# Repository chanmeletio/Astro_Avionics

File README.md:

# Astro at Baylor — Avionics Subsystem

Flight computer, sensor acquisition, dual-deployment recovery actuation, and telemetry subsystem developed by **Astro at Baylor** for the **2027 Intercollegiate Rocket Engineering Competition (IREC)** at Spaceport America.

---

## Subsystem Architecture

```
Astro_Avionics/
├── .github/
│   ├── workflows/          # Automated CI/CD (KiCad v10 DRC/ERC, ARM GCC cross-compilation)
│   ├── ISSUE_TEMPLATE/     # Hardware ECO, firmware bug, and flight anomaly reports
│   └── PULL_REQUEST_TEMPLATE.md
├── docs/                   # Flight documentation, state machines, pinouts, and link budgets
├── firmware/
│   ├── app/                # Flight state machine, telemetry dispatcher, and mission logic
│   ├── bsp/                # Board Support Package for Astro Flight Computer
│   ├── cube/               # STM32CubeMX HAL initialization and CMSIS DSP libraries
│   ├── drivers/            # Sensor drivers (Baro, High-G & Low-G IMUs, GPS, Radio, MicroSD)
│   ├── mid/                # Middleware (ring buffers, comms framing, RTOS abstractions)
│   └── tests/              # Native host unit tests and simulation mocks
├── ground-station/         # Real-time telemetry receiver, packet decoder, and mission UI
├── hardware/
│   ├── drc/                # KiCad Design Rule constraints and automated DRC check scripts
│   ├── libraries/          # Custom team footprint, symbol, and 3D model libraries
│   └── rev_a/              # KiCad v10 Flight Controller schematics, layouts, and manufacturing outputs
└── sim/                    # Software-in-the-Loop (SITL) and Hardware-in-the-Loop (HIL) simulators
```

---

## Hardware Overview (Rev A)

The Astro Avionics Flight Controller is designed in **KiCad v10** to withstand high acceleration, vibration, and thermal environments typical of supersonic high-power rocket flights.

* **Primary Processing Unit**: STM32F405RGT6 (Arm Cortex-M4 with FPU @ 168 MHz)
* **Inertial Sensing**:
  * High-G Triaxial Accelerometer (high-velocity boost phase acquisition)
  * Low-G 6-DOF IMU (apogee detection, attitude estimation, and descent tracking)
* **Barometric Altimetry**: High-precision barometric pressure sensor for altitude & apogee determination
* **Recovery & Pyrotechnics**: Dual-deployment pyro firing channels (Drogue @ Apogee, Main @ configured AGL altitude) with hardware interlocks and live continuity sensing
* **Telemetry & RF**: Long-range transceiver for live flight telemetry packet transmission to the ground station
* **Non-Volatile Logging**: MicroSD card interface logging sensor telemetry at high rates

For complete design files, see [`hardware/rev_a/`](hardware/rev_a/).

---

## Toolchain & Developer Prerequisites

### 1. Hardware Engineering (KiCad EDA)
* **KiCad v10** (or compatible KiCad 10 nightly build)
* KiCad CLI (`kicad-cli`) installed on system PATH for running local DRC/ERC exports

### 2. Embedded Firmware
* **ARM Embedded Toolchain**: `arm-none-eabi-gcc` (v10+ recommended)
* **Build Systems**: `cmake` (v3.22+) and `ninja-build` or GNU `make`
* **Static Analysis**: `clang-format` and `cppcheck`
* **Flashing & Debugging**: ST-LINK / J-Link with `openocd` or STM32CubeProgrammer

### 3. Simulation & Ground Station
* **Python**: Python 3.10+ with `pip` and virtual environment support

---

## Quickstart Guide

### Building Firmware Locally
```bash
# Clone the repository
git clone https://github.com/chanmeletio/Astro_Avionics.git
cd Astro_Avionics

# Configure and build firmware
cmake -B firmware/build -S firmware -DCMAKE_TOOLCHAIN_FILE=cmake/arm-none-eabi.cmake -GNinja
cmake --build firmware/build
```

### Running Hardware DRC & ERC Headless
```bash
# Run KiCad Electrical Rules Check
kicad-cli sch erc --output hardware/rev_a/output/erc_report.json hardware/rev_a/New_Flight_Controller.kicad_sch

# Run KiCad Design Rules Check
kicad-cli pcb drc --output hardware/rev_a/output/drc_report.json hardware/rev_a/New_Flight_Controller.kicad_pcb

# Parse violations with gatekeeper script
python hardware/drc/drc-ci-check.py --drc hardware/rev_a/output/drc_report.json --erc hardware/rev_a/output/erc_report.json
```

---

## Safety Protocol & Mission Rules

> [!CAUTION]
> **Pyrotechnic Safety Interlock Rule**: No live e-matches or pyrotechnic charges may be connected to the flight computer in the laboratory without the physical arming key / safety shunt removed and verified with a multimeter. Live fire testing must strictly adhere to [`docs/safety_procedures.md`](docs/safety_procedures.md).

---

## Contributing & Development Workflow

1. Create a feature branch from `develop` (`feat/driver-bmi088`, `hw/rev-a-power-trace-update`).
2. Ensure DRC/ERC passes with zero errors before opening a pull request.
3. Submit a Pull Request targeting `develop` using the provided [Pull Request Template](.github/PULL_REQUEST_TEMPLATE.md).

## License

This project is licensed under the [MIT License](LICENSE).

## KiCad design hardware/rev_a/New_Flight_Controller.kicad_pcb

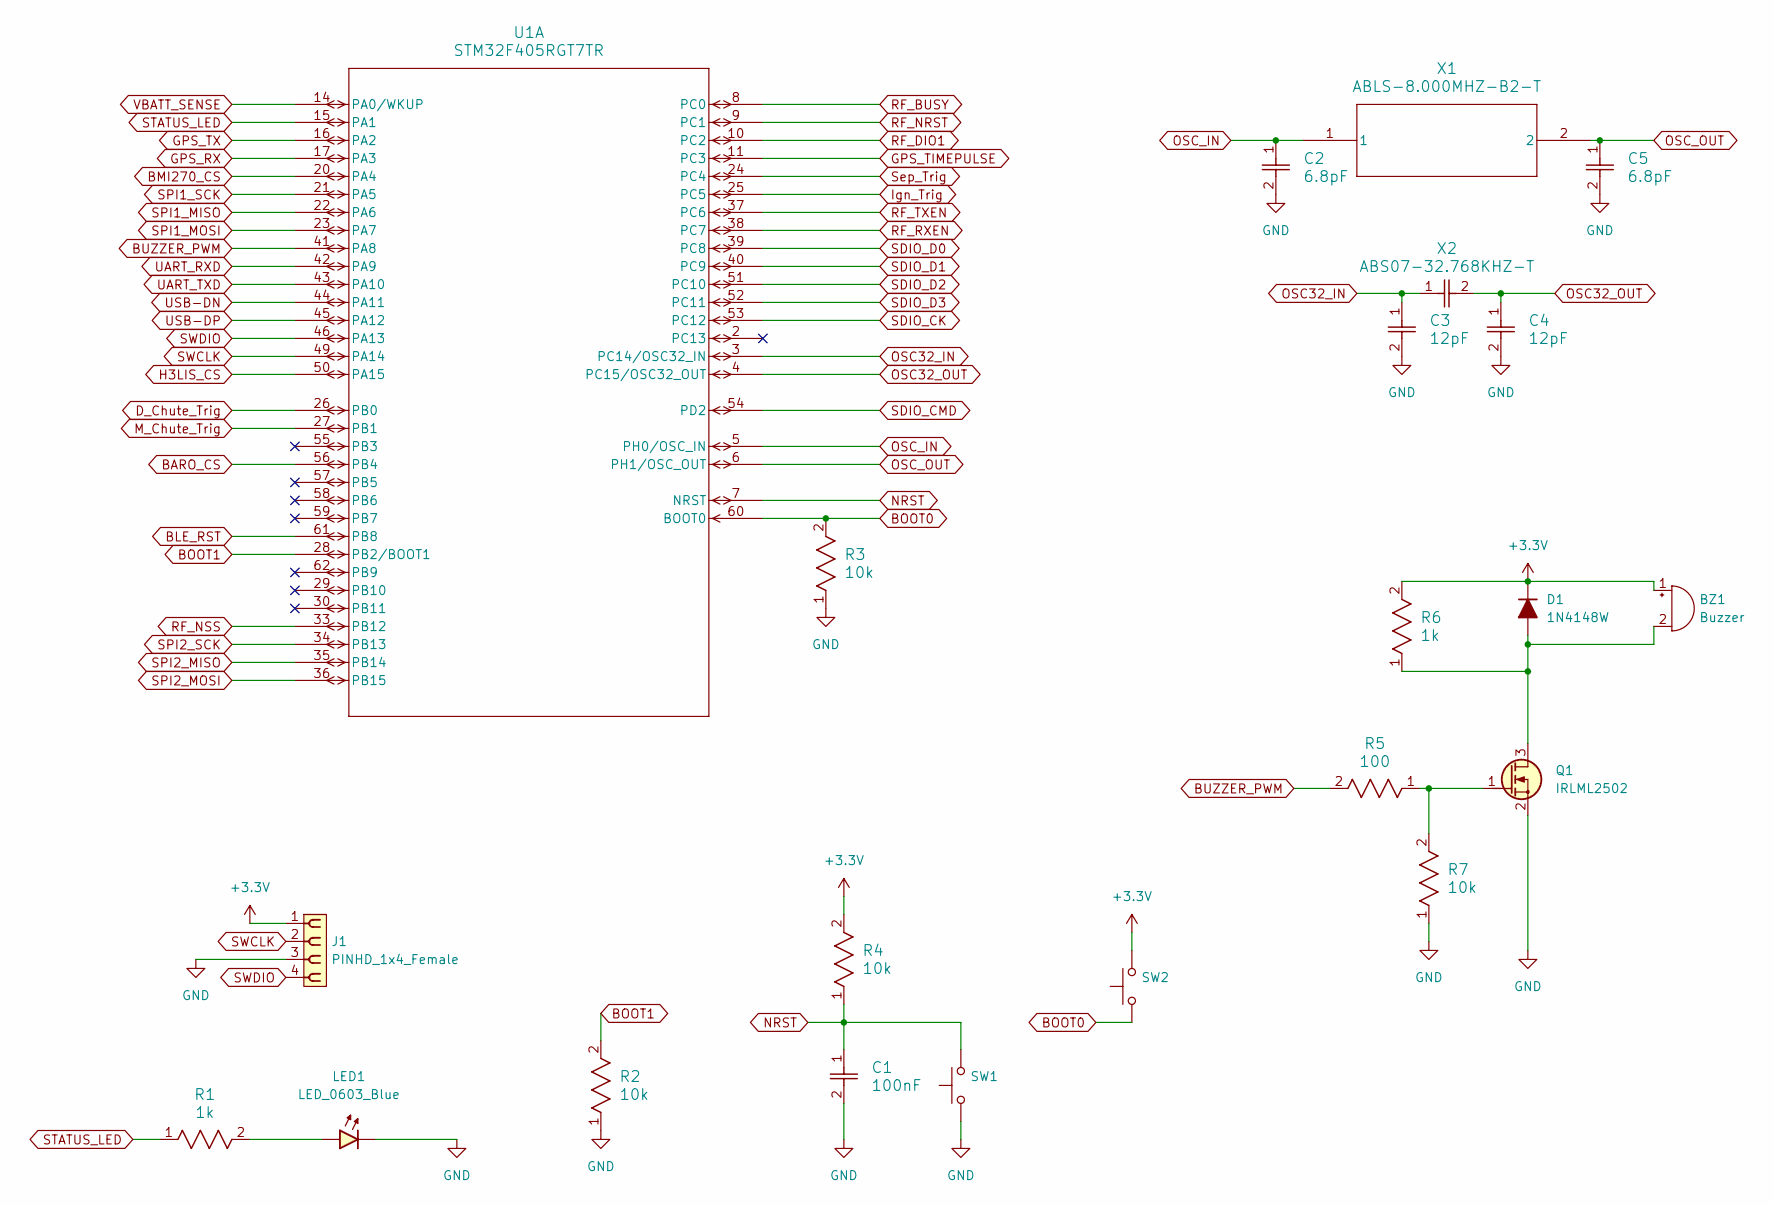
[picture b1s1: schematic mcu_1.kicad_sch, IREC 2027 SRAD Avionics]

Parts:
BZ1: Buzzer; Buzzer_Murata_PKMCS0909E; Mfg Part# PKMCS0909E4000-R1; JLCPCB Part # C910763
C1: 100nF; C_0603_1608Metric; Mfg Part# CL10B104KB8NNNC; JLCPCB Part # C1591
C2, C5: 6.8pF; C_0603_1608Metric; Mfg Part# CL10C6R8CB8NNNC; JLCPCB Part # C318672
C3, C4: 12pF; C_0603_1608Metric; Mfg Part# CL10C120JB8NNNC; JLCPCB Part # C38523
D1: 1N4148W; D_SOD-123; Mfg Part# 1N4148W; JLCPCB Part # C81598
J1: PINHD_1x4_Female; PinSocket_1x04_P2.54mm_Vertical; Mfg Part# 22850104ANG1SYA01; JLCPCB Part # C41431927
LED1: LED_0603_Blue; LED_0603_1608Metric; Mfg Part# KT-0603B; JLCPCB Part # C2288
Q1: IRLML2502; SOT-23; Mfg Part# IRLML2502TRPBF-ES; JLCPCB Part # C21713837
R1, R6: 1k; R_0603_1608Metric; Mfg Part# RC0603JR-071KL; JLCPCB Part # C14676
R2, R3, R4, R7: 10k; R_0603_1608Metric; Mfg Part# RC0603JR-0710KL; JLCPCB Part # C99198
R5: 100; R_0603_1608Metric; Mfg Part# RC0603FR-07100RL; JLCPCB Part # C105588
SW1, SW2: SW_Push_1P1T_NO_E-Switch_TL3301NxxxxxG; Mfg Part# 4-1437565-1; JLCPCB Part # C592734
U1: STM32F405RGT7TR; LQFP64-10x10mm; Mfg Part# STM32F405RGT7TR; JLCPCB Part # C2054405
X1: ABLS-8.000MHZ-B2-T; ABLS-8.000MHZ-B2-T_ABR; Mfg Part# ABLS-8.000MHZ-B2-T; JLCPCB Part # C596837
X2: ABS07-32.768KHZ-T; CAP_ABS07-32.768KHZ-T_ABR; Mfg Part# ABS07-32.768KHZ-T; JLCPCB Part # C130253

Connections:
+3.3V: BZ1.1 (+), D1.1 (K), J1.1, R4.2, R6.2, SW2.2; also elsewhere on the board
BARO_CS: U1.56 (PB4); also elsewhere on the board
BLE_RST: U1.61 (PB8); also elsewhere on the board
BMI270_CS: U1.20 (PA4); also elsewhere on the board
BOOT0: R3.2, SW2.1, U1.60 (BOOT0)
BOOT1: R2.2, U1.28 (PB2/BOOT1)
BUZZER_PWM: R5.2, U1.41 (PA8)
D_Chute_Trig: U1.26 (PB0); also elsewhere on the board
GND: C1.2, C2.2, C3.2, C4.2, C5.2, J1.3, LED1.1 (K), Q1.2 (S), R2.1, R3.1, R7.1, SW1.1; also elsewhere on the board
GPS_RX: U1.17 (PA3); also elsewhere on the board
GPS_TIMEPULSE: U1.11 (PC3); also elsewhere on the board
GPS_TX: U1.16 (PA2); also elsewhere on the board
H3LIS_CS: U1.50 (PA15); also elsewhere on the board
Ign_Trig: U1.25 (PC5); also elsewhere on the board
M_Chute_Trig: U1.27 (PB1); also elsewhere on the board
NRST: C1.1, R4.1, SW1.2, U1.7 (NRST)
unnamed: BZ1.2 (-), D1.2 (A), Q1.3 (D), R6.1
unnamed: LED1.2 (A), R1.2
unnamed: Q1.1 (G), R5.1, R7.2
OSC32_IN: C3.1, U1.3 (PC14/OSC32_IN), X2.1
OSC32_OUT: C4.1, U1.4 (PC15/OSC32_OUT), X2.2
OSC_IN: C2.1, U1.5 (PH0/OSC_IN), X1.1
OSC_OUT: C5.1, U1.6 (PH1/OSC_OUT), X1.2
RF_BUSY: U1.8 (PC0); also elsewhere on the board
RF_DIO1: U1.10 (PC2); also elsewhere on the board
RF_NRST: U1.9 (PC1); also elsewhere on the board
RF_NSS: U1.33 (PB12); also elsewhere on the board
RF_RXEN: U1.38 (PC7); also elsewhere on the board
RF_TXEN: U1.37 (PC6); also elsewhere on the board
SDIO_CK: U1.53 (PC12); also elsewhere on the board
SDIO_CMD: U1.54 (PD2); also elsewhere on the board
SDIO_D0: U1.39 (PC8); also elsewhere on the board
SDIO_D1: U1.40 (PC9); also elsewhere on the board
SDIO_D2: U1.51 (PC10); also elsewhere on the board
SDIO_D3: U1.52 (PC11); also elsewhere on the board
SPI1_MISO: U1.22 (PA6); also elsewhere on the board
SPI1_MOSI: U1.23 (PA7); also elsewhere on the board
SPI1_SCK: U1.21 (PA5); also elsewhere on the board
SPI2_MISO: U1.35 (PB14); also elsewhere on the board
SPI2_MOSI: U1.36 (PB15); also elsewhere on the board
SPI2_SCK: U1.34 (PB13); also elsewhere on the board
STATUS_LED: R1.1, U1.15 (PA1)
SWCLK: J1.2, U1.49 (PA14)
SWDIO: J1.4, U1.46 (PA13)
Sep_Trig: U1.24 (PC4); also elsewhere on the board
UART_RXD: U1.42 (PA9); also elsewhere on the board
UART_TXD: U1.43 (PA10); also elsewhere on the board
USB-DN: U1.44 (PA11); also elsewhere on the board
USB-DP: U1.45 (PA12); also elsewhere on the board
VBATT_SENSE: U1.14 (PA0/WKUP); also elsewhere on the board

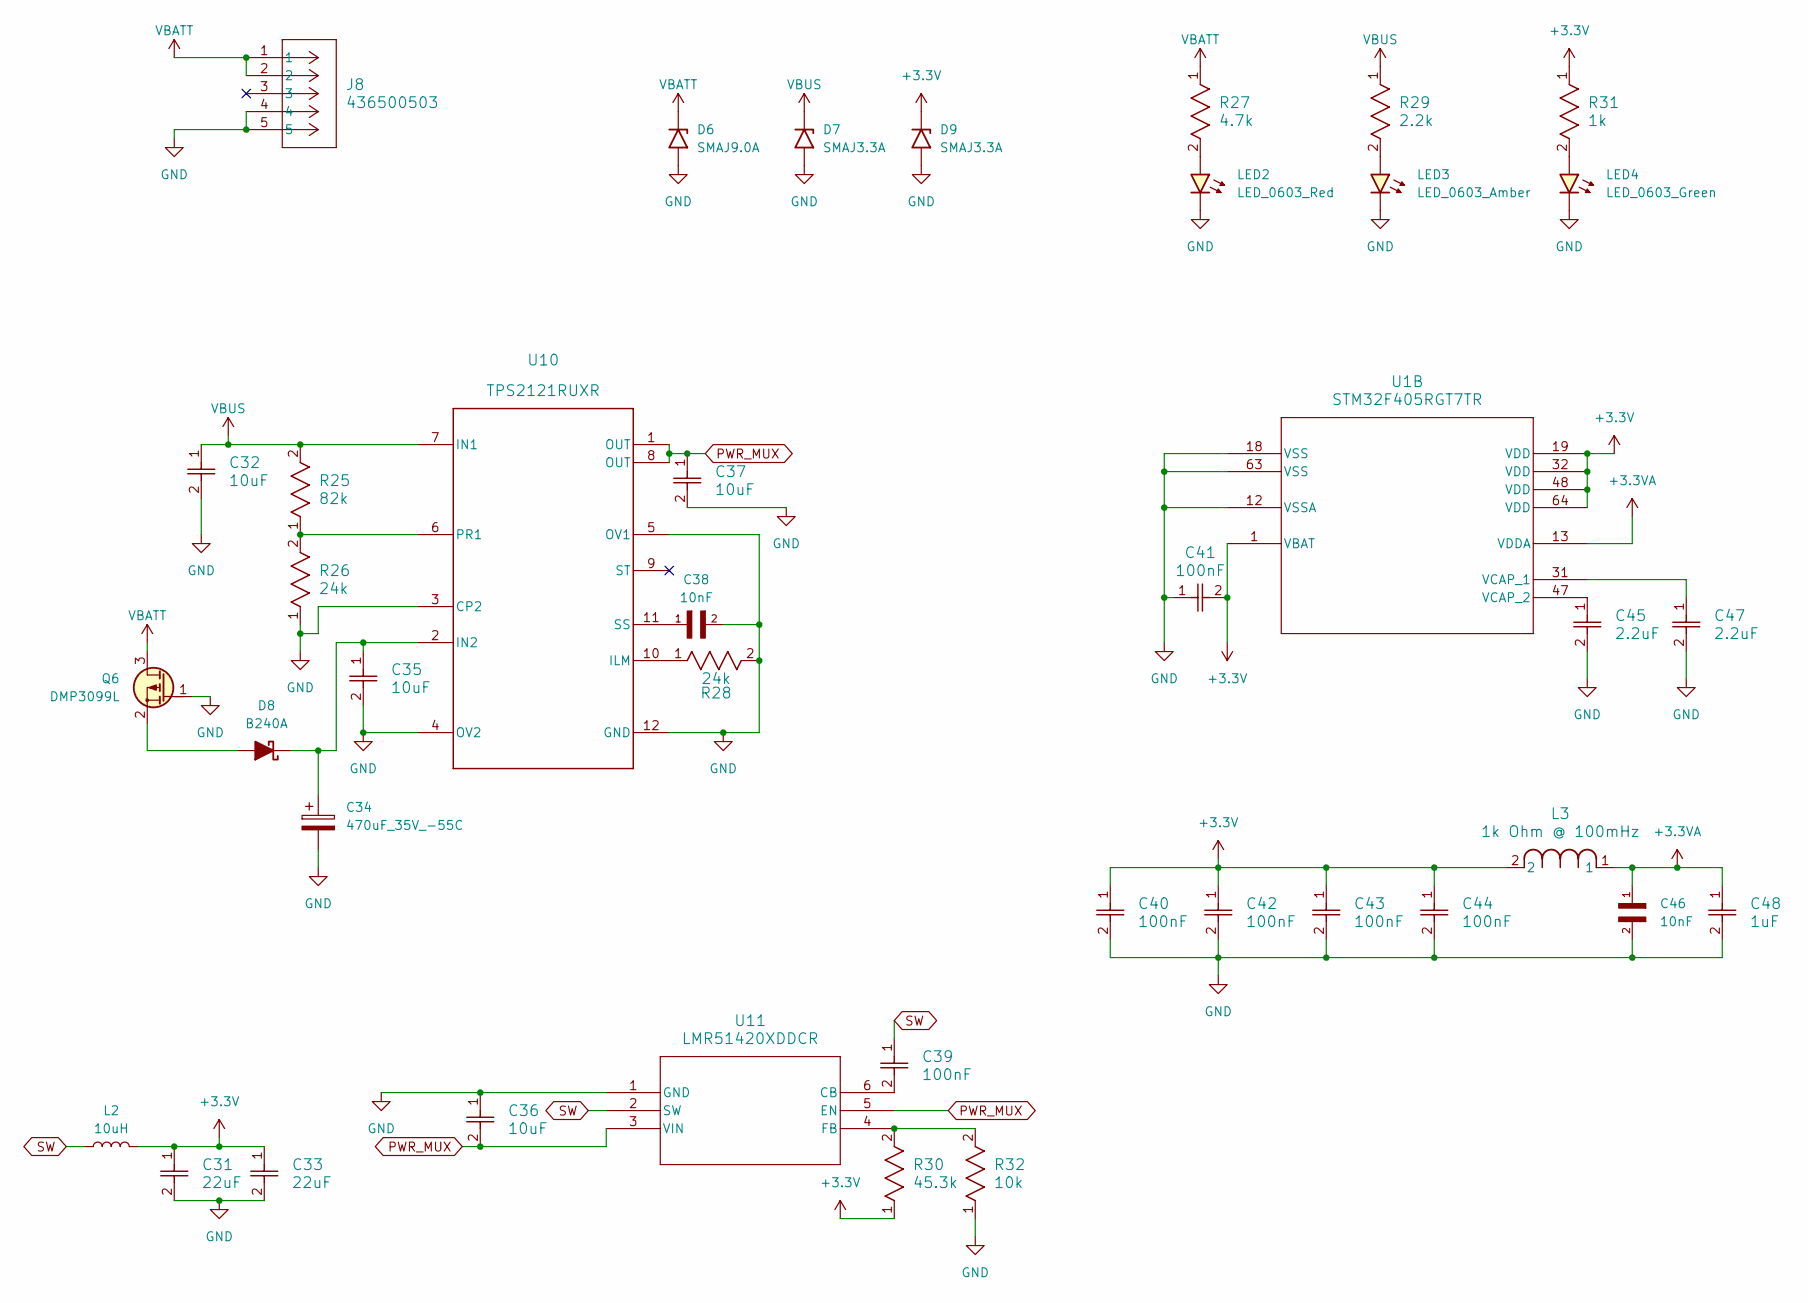
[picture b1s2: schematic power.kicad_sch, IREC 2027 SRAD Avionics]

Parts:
C31, C33: 22uF; C_0603_1608Metric; Mfg Part# CL10A226MP8NUNE; JLCPCB Part # C86295
C32, C35, C36, C37: 10uF; C_0603_1608Metric; Mfg Part# CL10A106MA8NRNC; JLCPCB Part # C96446
C34: 470uF_35V_-55C; C_Elec_10x10.2; Mfg Part# 189RV0073; JLCPCB Part # C18203153
C38, C46: 10nF; C_0603_1608Metric; Mfg Part# CL10B103KB8NNNC; JLCPCB Part # C1589
C39, C40, C41, C42, C43, C44: 100nF; C_0603_1608Metric; Mfg Part# CL10B104KB8NNNC; JLCPCB Part # C1591
C45, C47: 2.2uF; C_0603_1608Metric; Mfg Part# CL10B225KP8NNNC; JLCPCB Part # C100082
C48: 1uF; C_0603_1608Metric; Mfg Part# CL10B105KB8NQNC; JLCPCB Part # C5199872
D6: SMAJ9.0A; D_SMA; Mfg Part# SMAJ9.0A; JLCPCB Part # C113955
D7: SMAJ3.3A; D_SMA; Mfg Part# SMAJ3.3A; JLCPCB Part # C18199544
D8: B240A; D_SMA; Mfg Part# B240A; JLCPCB Part # C39358
D9: SMAJ3.3A; D_SMA; Mfg Part# SMAJ3.3A; JLCPCB Part # C2917853
J8: 436500503; CONN_SD-43650-002_05_MOL; Mfg Part# 436500503; JLCPCB Part # C19793673
L2: 10uH; L_0805_2012Metric; Mfg Part# MLF2012E100JT000; JLCPCB Part # C76742
L3: 1k Ohm @ 100mHz; Ferrite_0603_1608Metric; Mfg Part# BLM18KG102SH1D; JLCPCB Part # C883597
LED2: LED_0603_Red; LED_0603_1608Metric; Mfg Part# KT-0603R; JLCPCB Part # C2286
LED3: LED_0603_Amber; LED_0603_1608Metric; Mfg Part# KT-0603Y; JLCPCB Part # C2287
LED4: LED_0603_Green; LED_0603_1608Metric; Mfg Part# KT-0603G; JLCPCB Part # C12624
Q6: DMP3099L; SOT-23; Mfg Part# DMP3099L; JLCPCB Part # C2940610
R25: 82k; R_0603_1608Metric; Mfg Part# RC0603FR-0782KL; JLCPCB Part # C137678
R26, R28: 24k; R_0603_1608Metric; Mfg Part# 0603WAF2402T5E; JLCPCB Part # C23352
R27: 4.7k; R_0603_1608Metric; Mfg Part# RC0603FR-074K7L; JLCPCB Part # C99782
R29: 2.2k; R_0603_1608Metric; Mfg Part# RC0603FR-072K2L; JLCPCB Part # C114662
R30: 45.3k; R_0603_1608Metric; Mfg Part# AC0603FR-0745K3L; JLCPCB Part # C227910
R31: 1k; R_0603_1608Metric; Mfg Part# RC0603JR-071KL; JLCPCB Part # C14676
R32: 10k; R_0603_1608Metric; Mfg Part# RC0603JR-0710KL; JLCPCB Part # C99198
U1: STM32F405RGT7TR; LQFP64-10x10mm; Mfg Part# STM32F405RGT7TR; JLCPCB Part # C2054405
U10: TPS2121RUXR; RUX0012A; Mfg Part# TPS2121RUXR; JLCPCB Part # C485916
U11: LMR51420XDDCR; SOT23_DDC_TEX; Mfg Part# LMR51420XDDCR; JLCPCB Part # C5246146

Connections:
+3.3V: C31.1, C33.1, C40.1, C41.2, C42.1, C43.1, C44.1, D9.1 (A1), L2.2, L3.2, R30.1, R31.1, U1.1 (VBAT), U1.19 (VDD), U1.32 (VDD), U1.48 (VDD), U1.64 (VDD); also elsewhere on the board
+3.3VA: C46.1, C48.1, L3.1, U1.13 (VDDA)
GND: C31.2, C32.2, C33.2, C34.2, C35.2, C36.1, C37.2, C38.2, C40.2, C41.1, C42.2, C43.2, C44.2, C45.2, C46.2, C47.2, C48.2, D6.2 (A2), D7.2 (A2), D9.2 (A2), J8.4, J8.5, LED2.1 (K), LED3.1 (K), LED4.1 (K), Q6.1 (G), R26.1, R28.2, R32.1, U1.12 (VSSA), U1.18 (VSS), U1.63 (VSS), U10.3 (CP2), U10.4 (OV2), U10.5 (OV1), U10.12 (GND), U11.1 (GND); also elsewhere on the board
unnamed: D8.2 (A), Q6.2 (S)
unnamed: C34.1, C35.1, D8.1 (K), U10.2 (IN2)
unnamed: LED2.2 (A), R27.2
unnamed: LED3.2 (A), R29.2
unnamed: LED4.2 (A), R31.2
unnamed: C47.1, U1.31 (VCAP_1)
unnamed: C45.1, U1.47 (VCAP_2)
unnamed: R28.1, U10.10 (ILM)
unnamed: R25.1, R26.2, U10.6 (PR1)
unnamed: C38.1, U10.11 (SS)
unnamed: C39.2, U11.6 (CB)
unnamed: R30.2, R32.2, U11.4 (FB)
PWR_MUX: C36.2, C37.1, U10.1 (OUT), U10.8 (OUT), U11.3 (VIN), U11.5 (EN)
SW: C39.1, L2.1, U11.2 (SW)
VBATT: D6.1 (A1), J8.1, J8.2, Q6.3 (D), R27.1; also elsewhere on the board
VBUS: C32.1, D7.1 (A1), R25.2, R29.1, U10.7 (IN1); also elsewhere on the board

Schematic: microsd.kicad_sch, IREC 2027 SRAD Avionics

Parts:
C21, C23: 100nF; C_0603_1608Metric; Mfg Part# CL10B104KB8NNNC; JLCPCB Part # C1591
C22: 4.7uF; C_0603_1608Metric; Mfg Part# CL10A475KO8NNNC; JLCPCB Part # C19666
J3: 472192001; CONN_47219-2001_MOL; Mfg Part# 472192001; JLCPCB Part # C164170
R11, R12: 5.1k; R_0603_1608Metric; Mfg Part# RC0603FR-075K1L; JLCPCB Part # C105580
R13: 10k; R_0603_1608Metric; Mfg Part# RC0603JR-0710KL; JLCPCB Part # C99198
RN1: R_10k_4x1206; R_Array_Concave_4x0603; Mfg Part# YC164-FR-0710KL; JLCPCB Part # C110924
U7: TPD4E001DBVR; SOT-23-6; Mfg Part# TPD4E001DBVR; JLCPCB Part # C465736
U8: 2137160001; 2137160001_MOL; Mfg Part# 213716-0001; JLCPCB Part # C5119949

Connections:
+3.3V: C22.1, C23.1, J3.4, R13.1, RN1.1 (R1.1), RN1.2 (R2.1), RN1.3 (R3.1), RN1.4 (R4.1); also elsewhere on the board
CC1: R11.1, U7.3 (IO2), U8.A5 (CC1)
CC2: R12.2, U7.4 (IO3), U8.B5 (CC2)
GND: C21.2, C22.2, C23.2, J3.6, R11.2, R12.1, U7.2 (GND), U8.A1 (GND), U8.A12 (GND), U8.B1 (GND), U8.B12 (GND); also elsewhere on the board
SDIO_CK: J3.5; also elsewhere on the board
SDIO_CMD: J3.3, RN1.6 (R3.2); also elsewhere on the board
SDIO_D0: J3.7, R13.2; also elsewhere on the board
SDIO_D1: J3.8, RN1.5 (R4.2); also elsewhere on the board
SDIO_D2: J3.1, RN1.8 (R1.2); also elsewhere on the board
SDIO_D3: J3.2, RN1.7 (R2.2); also elsewhere on the board
USB-DN: U7.6 (IO4), U8.A7 (DN1), U8.B7 (DN2); also elsewhere on the board
USB-DP: U7.1 (IO1), U8.A6 (DP1), U8.B6 (DP2); also elsewhere on the board
VBUS: C21.1, U7.5 (VCC), U8.A4 (VBUS), U8.A9 (VBUS), U8.B4 (VBUS), U8.B9 (VBUS); also elsewhere on the board

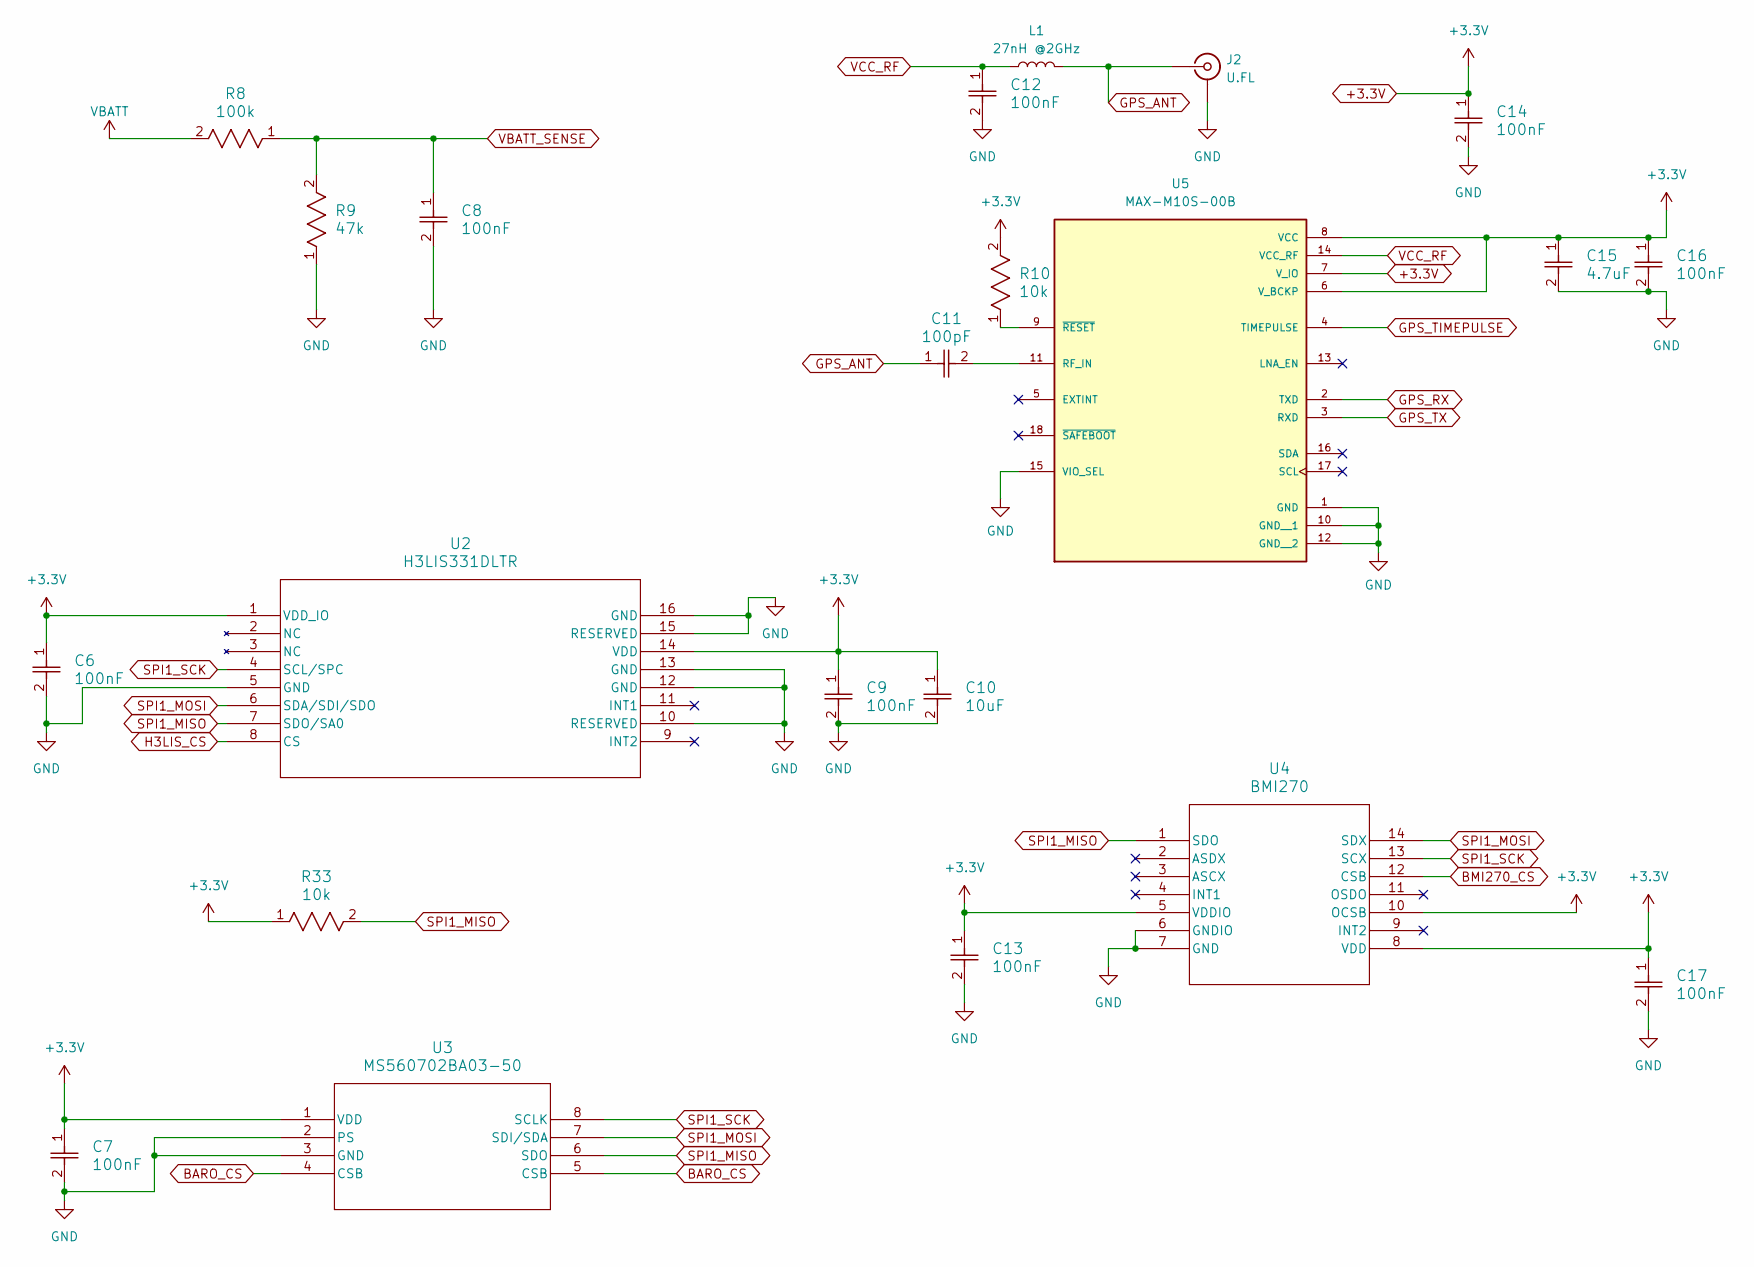
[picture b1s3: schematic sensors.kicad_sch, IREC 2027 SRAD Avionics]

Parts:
C6, C7, C8, C9, C12, C13, C14, C16, C17: 100nF; C_0603_1608Metric; Mfg Part# CL10B104KB8NNNC; JLCPCB Part # C1591
C10: 10uF; C_0603_1608Metric; Mfg Part# CL10A106MA8NRNC; JLCPCB Part # C96446
C11: 100pF; C_0603_1608Metric; Mfg Part# CL10C101JB8NNNC; JLCPCB Part # C14858
C15: 4.7uF; C_0603_1608Metric; Mfg Part# CL10A475KO8NNNC; JLCPCB Part # C19666
J2: U.FL; Mfg Part# BWU.FL-IPEX1; JLCPCB Part # C5137195
L1: 27nH @2GHz; L_0603_1608Metric; Mfg Part# SDCL0603Q27NJT02B02; JLCPCB Part # C279522
R8: 100k; R_0603_1608Metric; Mfg Part# RC0603FR-07100KL; JLCPCB Part # C14675
R9: 47k; R_0603_1608Metric; Mfg Part# AC0603FR-0747KL; JLCPCB Part # C111134
R10, R33: 10k; R_0603_1608Metric; Mfg Part# RC0603JR-0710KL; JLCPCB Part # C99198
U2: H3LIS331DLTR; QFN_31DLTR_STM; Mfg Part# H3LIS331DLTR; JLCPCB Part # C2655074
U3: MS560702BA03-50; SON8_MS5611_TEC; Mfg Part# MS560702BA03-50; JLCPCB Part # C97627
U4: BMI270; BMI270_BOS; Mfg Part# BMI270; JLCPCB Part # C2836813
U5: MAX-M10S-00B; XCVR_MAX-M10S-00B; PARTREV C1; JLCPCB Part # C4153167

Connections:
+3.3V: C6.1, C7.1, C9.1, C10.1, C13.1, C14.1, C15.1, C16.1, C17.1, R10.2, R33.1, U2.1 (VDD_IO), U2.14 (VDD), U3.1 (VDD), U4.5 (VDDIO), U4.8 (VDD), U4.10 (OCSB), U5.6 (V_BCKP), U5.7 (V_IO), U5.8 (VCC); also elsewhere on the board
BARO_CS: U3.4 (CSB), U3.5 (CSB); also elsewhere on the board
BMI270_CS: U4.12 (CSB); also elsewhere on the board
GND: C6.2, C7.2, C8.2, C9.2, C10.2, C12.2, C13.2, C14.2, C15.2, C16.2, C17.2, J2.2 (Ext), R9.1, U2.5 (GND), U2.10 (RESERVED), U2.12 (GND), U2.13 (GND), U2.15 (RESERVED), U2.16 (GND), U3.2 (PS), U3.3 (GND), U4.6 (GNDIO), U4.7 (GND), U5.1 (GND), U5.10 (GND__1), U5.12 (GND__2), U5.15 (VIO_SEL); also elsewhere on the board
GPS_ANT: C11.1, J2.1 (In), L1.2
GPS_RX: U5.2 (TXD); also elsewhere on the board
GPS_TIMEPULSE: U5.4 (TIMEPULSE); also elsewhere on the board
GPS_TX: U5.3 (RXD); also elsewhere on the board
H3LIS_CS: U2.8 (CS); also elsewhere on the board
unnamed: C11.2, U5.11 (RF_IN)
unnamed: R10.1, U5.9 (~RESET)
SPI1_MISO: R33.2, U2.7 (SDO/SA0), U3.6 (SDO), U4.1 (SDO); also elsewhere on the board
SPI1_MOSI: U2.6 (SDA/SDI/SDO), U3.7 (SDI/SDA), U4.14 (SDX); also elsewhere on the board
SPI1_SCK: U2.4 (SCL/SPC), U3.8 (SCLK), U4.13 (SCX); also elsewhere on the board
VBATT: R8.2; also elsewhere on the board
VBATT_SENSE: C8.1, R8.1, R9.2; also elsewhere on the board
VCC_RF: C12.1, L1.1, U5.14 (VCC_RF)

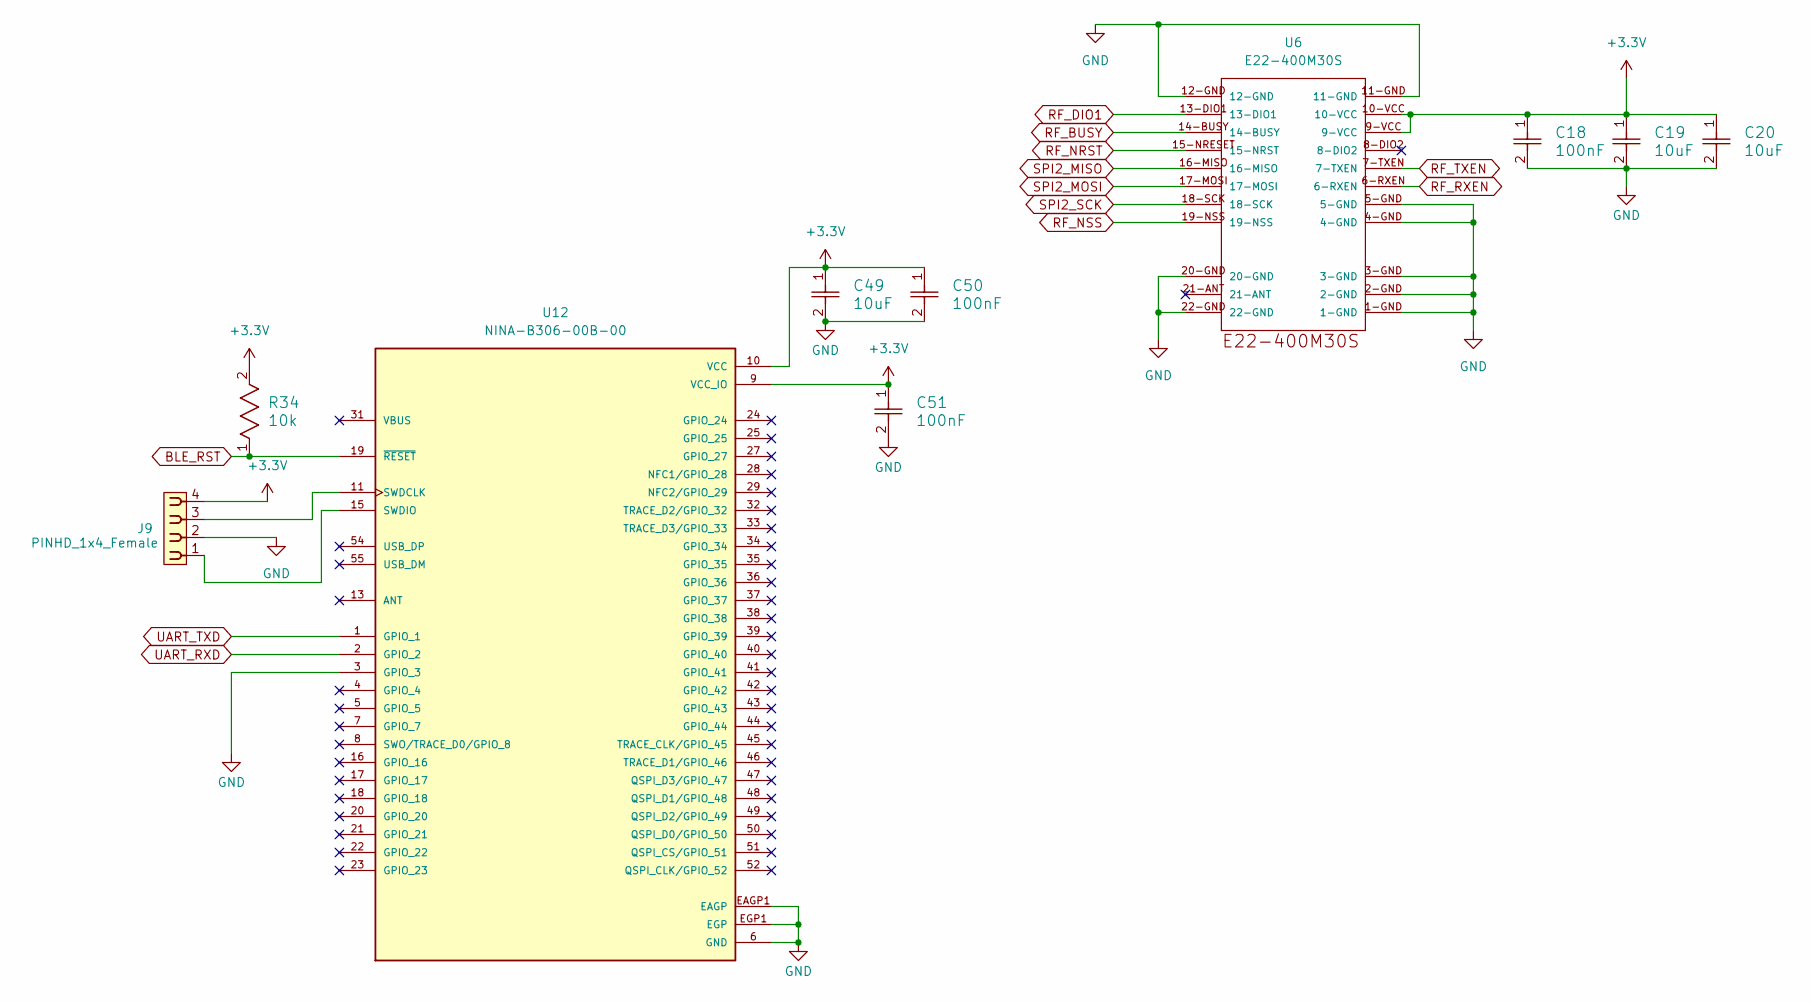
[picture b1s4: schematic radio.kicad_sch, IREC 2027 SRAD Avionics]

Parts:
C18, C50, C51: 100nF; C_0603_1608Metric; Mfg Part# CL10B104KB8NNNC; JLCPCB Part # C1591
C19, C20, C49: 10uF; C_0603_1608Metric; Mfg Part# CL10A106MA8NRNC; JLCPCB Part # C96446
J9: PINHD_1x4_Female; PinSocket_1x04_P2.54mm_Vertical; Mfg Part# 22850104ANG1SYA01; JLCPCB Part # C41431927
R34: 10k; R_0603_1608Metric; Mfg Part# RC0603JR-0710KL; JLCPCB Part # C99198
U6: E22-400M30S; Mfg Part# E22-400M30S; JLCPCB Part # C411292
U12: NINA-B306-00B-00; XCVR_NINA-B306-00B-00; PARTREV R07

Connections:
+3.3V: C18.1, C19.1, C20.1, C49.1, C50.1, C51.1, J9.4, R34.2, U6.9-VCC, U6.10-VCC, U12.9 (VCC_IO), U12.10 (VCC); also elsewhere on the board
BLE_RST: R34.1, U12.19 (~RESET); also elsewhere on the board
GND: C18.2, C19.2, C20.2, C49.2, C50.2, C51.2, J9.2, U6.1-GND, U6.2-GND, U6.3-GND, U6.4-GND, U6.5-GND, U6.11-GND, U6.12-GND, U6.20-GND, U6.22-GND, U12.3 (GPIO_3), U12.6 (GND), U12.12 (GND), U12.14 (GND), U12.26 (GND), U12.30 (GND), U12.53 (GND), U12.EAGP1 (EAGP), U12.EAGP2 (EAGP), U12.EAGP3 (EAGP), U12.EAGP4 (EAGP), U12.EGP1 (EGP), U12.EGP2 (EGP), U12.EGP3 (EGP), U12.EGP4 (EGP), U12.EGP5 (EGP), U12.EGP6 (EGP), U12.EGP7 (EGP), U12.EGP8 (EGP), U12.EGP9 (EGP), U12.EGP10 (EGP), U12.EGP11 (EGP), U12.EGP12 (EGP); also elsewhere on the board
unnamed: J9.3, U12.11 (SWDCLK)
unnamed: J9.1, U12.15 (SWDIO)
RF_BUSY: U6.14-BUSY; also elsewhere on the board
RF_DIO1: U6.13-DIO1; also elsewhere on the board
RF_NRST: U6.15-NRESET (15-NRST); also elsewhere on the board
RF_NSS: U6.19-NSS; also elsewhere on the board
RF_RXEN: U6.6-RXEN; also elsewhere on the board
RF_TXEN: U6.7-TXEN; also elsewhere on the board
SPI2_MISO: U6.16-MISO; also elsewhere on the board
SPI2_MOSI: U6.17-MOSI; also elsewhere on the board
SPI2_SCK: U6.18-SCK; also elsewhere on the board
UART_RXD: U12.2 (GPIO_2); also elsewhere on the board
UART_TXD: U12.1 (GPIO_1); also elsewhere on the board

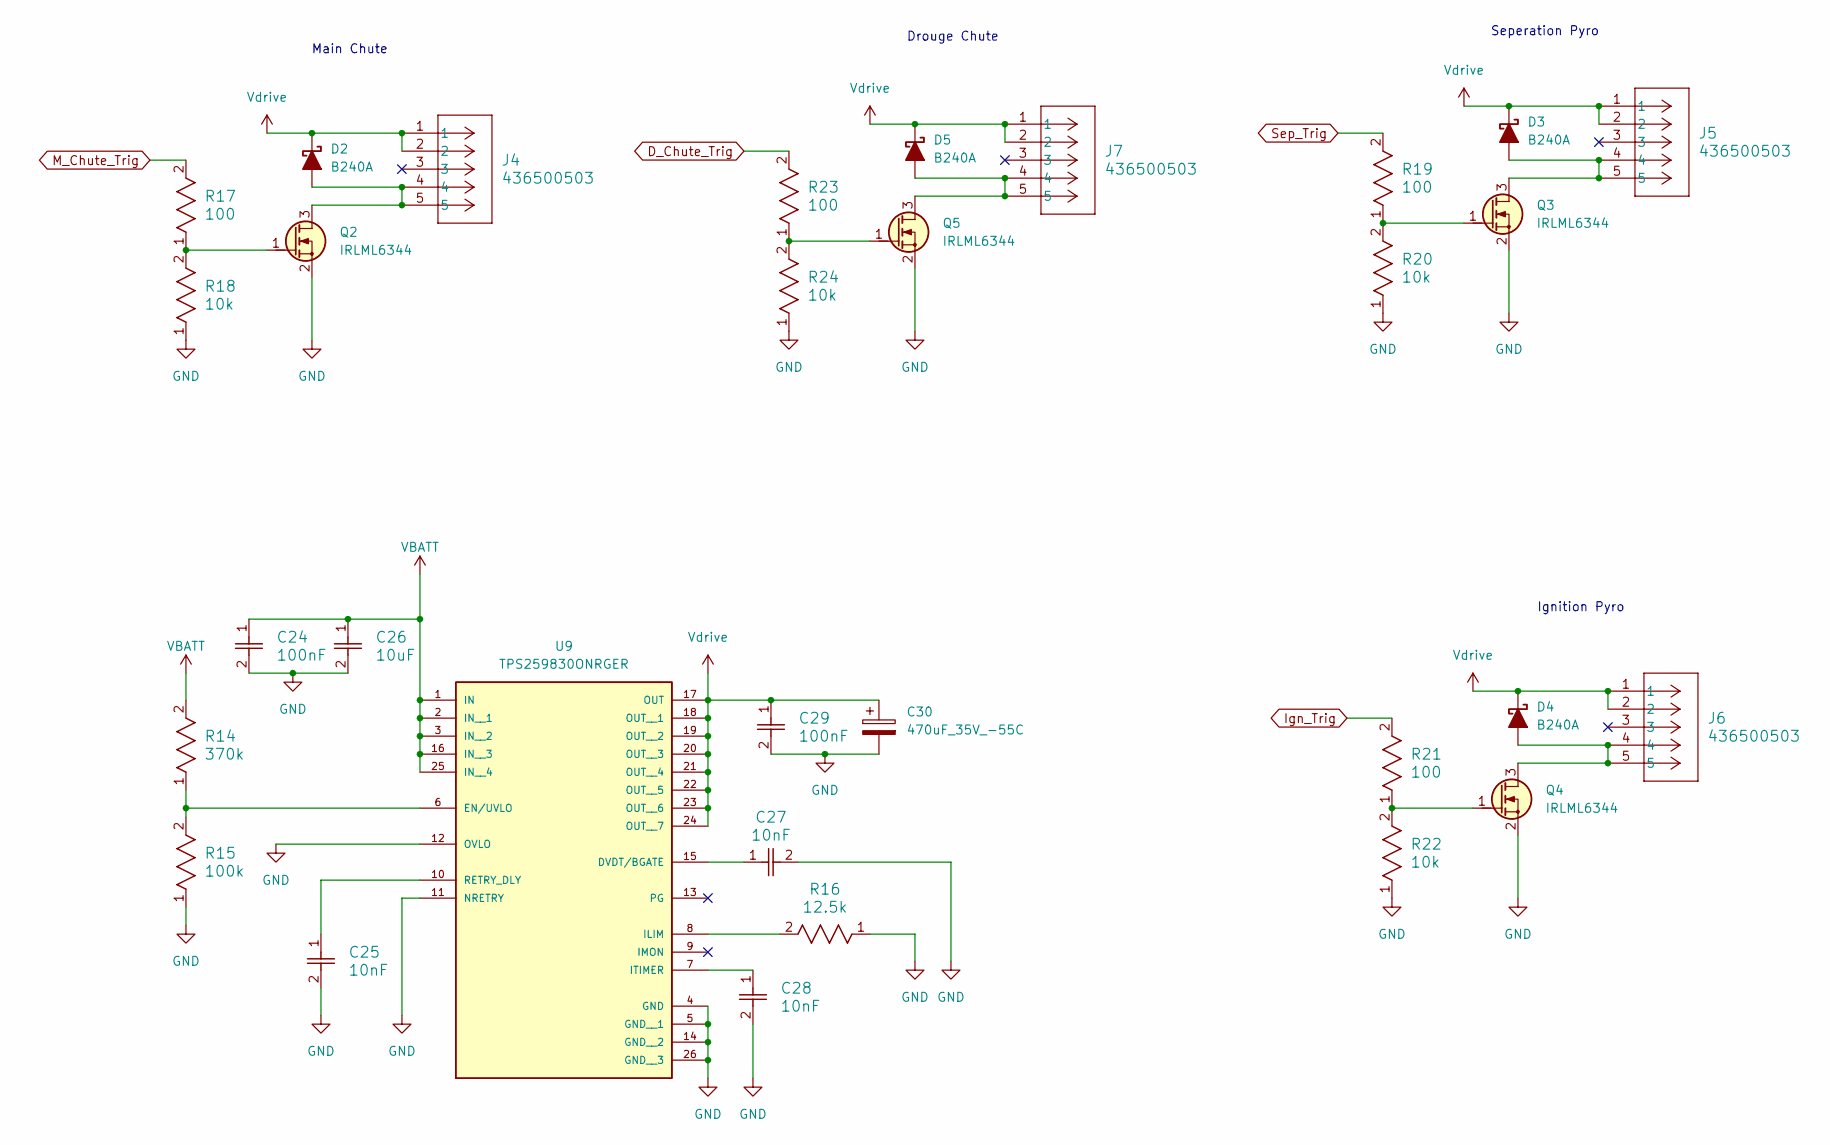
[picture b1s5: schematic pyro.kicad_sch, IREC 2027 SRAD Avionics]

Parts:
C24, C29: 100nF; C_0603_1608Metric; Mfg Part# CL10B104KB8NNNC; JLCPCB Part # C1591
C25, C27, C28: 10nF; C_0603_1608Metric; Mfg Part# CL10B103KB8NNNC; JLCPCB Part # C1589
C26: 10uF; C_0603_1608Metric; Mfg Part# CL10A106MA8NRNC; JLCPCB Part # C96446
C30: 470uF_35V_-55C; C_Elec_10x10.2; Mfg Part# 189RV0073; JLCPCB Part # C18203153
D2, D3, D4, D5: B240A; D_SMA; Mfg Part# B240A; JLCPCB Part # C39358
J4, J5, J6, J7: 436500503; CONN_SD-43650-002_05_MOL; Mfg Part# 436500503; JLCPCB Part # C19793673
Q2, Q3, Q4, Q5: IRLML6344; SOT-23; Mfg Part# IRLML6344TRPBF-HXY; JLCPCB Part # C6285738
R14: 370k; R_1206_3216Metric; Mfg Part# SCR1206J370K; JLCPCB Part # C3018094
R15: 100k; R_0603_1608Metric; Mfg Part# RC0603FR-07100KL; JLCPCB Part # C14675
R16: 12.5k; R_0603_1608Metric; Mfg Part# MF1/8W ±1% 12K5 OTB5; JLCPCB Part # C337058
R17, R19, R21, R23: 100; R_0603_1608Metric; Mfg Part# RC0603FR-07100RL; JLCPCB Part # C105588
R18, R20, R22, R24: 10k; R_0603_1608Metric; Mfg Part# RC0603JR-0710KL; JLCPCB Part # C99198
U9: TPS259830ONRGER; IC_TPS259830LNRGER; PARTREV B; JLCPCB Part # C20611808

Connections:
D_Chute_Trig: R23.2; also elsewhere on the board
GND: C24.2, C25.2, C26.2, C27.2, C28.2, C29.2, C30.2, Q2.2 (S), Q3.2 (S), Q4.2 (S), Q5.2 (S), R15.1, R16.1, R18.1, R20.1, R22.1, R24.1, U9.4 (GND), U9.5 (GND__1), U9.11 (NRETRY), U9.12 (OVLO), U9.14 (GND__2), U9.26 (GND__3); also elsewhere on the board
Ign_Trig: R21.2; also elsewhere on the board
M_Chute_Trig: R17.2; also elsewhere on the board
unnamed: D2.2 (A), J4.4, J4.5, Q2.3 (D)
unnamed: D3.2 (A), J5.4, J5.5, Q3.3 (D)
unnamed: D4.2 (A), J6.4, J6.5, Q4.3 (D)
unnamed: D5.2 (A), J7.4, J7.5, Q5.3 (D)
unnamed: Q2.1 (G), R17.1, R18.2
unnamed: Q3.1 (G), R19.1, R20.2
unnamed: Q4.1 (G), R21.1, R22.2
unnamed: Q5.1 (G), R23.1, R24.2
unnamed: C27.1, U9.15 (DVDT/BGATE)
unnamed: R14.1, R15.2, U9.6 (EN/UVLO)
unnamed: R16.2, U9.8 (ILIM)
unnamed: C28.1, U9.7 (ITIMER)
unnamed: C25.1, U9.10 (RETRY_DLY)
Sep_Trig: R19.2; also elsewhere on the board
VBATT: C24.1, C26.1, R14.2, U9.1 (IN), U9.2 (IN__1), U9.3 (IN__2), U9.16 (IN__3), U9.25 (IN__4); also elsewhere on the board
Vdrive: C29.1, C30.1, D2.1 (K), D3.1 (K), D4.1 (K), D5.1 (K), J4.1, J4.2, J5.1, J5.2, J6.1, J6.2, J7.1, J7.2, U9.17 (OUT), U9.18 (OUT__1), U9.19 (OUT__2), U9.20 (OUT__3), U9.21 (OUT__4), U9.22 (OUT__5), U9.23 (OUT__6), U9.24 (OUT__7)

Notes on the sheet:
Drouge Chute
Seperation Pyro
Main Chute
Ignition Pyro

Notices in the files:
README.md:
License: MIT
